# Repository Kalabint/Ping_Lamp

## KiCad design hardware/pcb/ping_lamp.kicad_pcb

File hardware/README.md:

# Ping Lamp hardware: driver board and base for a Harmony XVU tower

Round driver PCB (54 mm) and a 3D-printed base ring (60 mm) that sit between a base plate and a
Schneider Electric Harmony XVU signal tower with 24 V AC/DC red, orange and green units.
One USB cable supplies the lamp and is also the programming port.

## Status

| Item | State |
|---|---|
| Netlist | Checked by script: schematic = PCB = `pcb/design.py` (131 pins) |
| Routing | Complete, 0 unconnected, 68 ground stitching vias |
| DRC (KiCad 7.0.11) | No clearance, short or edge errors. A few silkscreen notes. The 47 `lib_footprint_issues` entries in `pcb/fab/ping_lamp_drc.txt` only say that the build machine had no footprint library table. |
| Independent review | One review by a second reviewer without access to the design history; its findings are fixed or listed under "Open points" |
| Prototype | **None built.** Nothing here has been tested on hardware. |

Read "Open points" before ordering.

## Files

| Path | Content |
|---|---|
| [`docs/datasheet.md`](docs/datasheet.md) | Datasheet: ratings, electrical design values, connectors, mechanical data |
| [`docs/manual.md`](docs/manual.md) | Assembly and operating manual |
| `pcb/design.py` | Parts, netlist, placement, pre-laid tracks. Edit this, not the KiCad files. |
| `pcb/generate.py` | Builds schematic, routed PCB and `pcb/fab/` from `design.py` |
| `pcb/ping_lamp.kicad_*` | KiCad 7 project (generated) |
| `pcb/fab/ping_lamp_gerber.zip` | Gerber and drill files |
| `pcb/fab/ping_lamp_bom.csv`, `ping_lamp_cpl.csv` | Parts list and placement file in JLCPCB column layout |
| `pcb/fab/*.pdf` | Schematic and both copper sides |
| `enclosure/ping_lamp_base.scad` | Parametric base ring (OpenSCAD) |
| `enclosure/*.stl` | Tray and lid, exported with the default parameters |

## Circuit

| Block | Parts | Notes |
|---|---|---|
| Input | USB-C (J1), 5.1 k on CC1/CC2, PTC fuse 1.1 A (F1), USBLC6-2SC6 (U4) | Optional solder pads J4 "5V IN" in parallel to USB VBUS |
| 3.3 V | AP2112K-3.3 (U2) | Supplies the ESP32 module |
| 24 V | MT3608 boost (U3), 22 uH (L1), SS34 (D1), 390 k / 10 k divider | Vout = 0.6 V x (1 + 390/10) = 24.0 V. Enable is pulled down: the rail is **off until the firmware drives GPIO10 high** |
| Controller | ESP32-C3-WROOM-02-N4 (U1) | Native USB serial/JTAG on GPIO18/19, no USB-UART bridge |
| Outputs | 4 x AO3422 low-side (Q1..Q4), 100 R gate, 10 k pull-down | Tower common is +24 V, each tier returns through one MOSFET |

With the boost disabled the "+24V" terminal still carries about 4.5 V (USB voltage through L1
and D1). That is how a boost converter behaves; it is not a fault.

### GPIO map

| GPIO | Function |
|---|---|
| 4 | Green tier (Q1) |
| 5 | Orange tier (Q2) |
| 6 | Red tier (Q3) |
| 7 | AUX output (Q4), e.g. buzzer unit |
| 10 | Boost enable, high = 24 V on |
| 8 | Status LED, active low (strapping pin, pulled up) |
| 9 | BOOT button (SW1) |
| 0, 1 | Expansion header J3 (IO0, IO1, 3V3, GND), not populated |
| 2 | Pulled up (strapping pin) |

Firmware: in `ESP32/main.py` set `PIN_NUM_GREEN = 4`, `PIN_NUM_ORANGE = 5`, `PIN_NUM_RED = 6`,
`PIN_NUM_BOOST_EN = 10` and flash the MicroPython build for ESP32-C3. The defaults in that
file are for the breadboard version; on this board they would drive the USB pins.

### Terminal J2 (wire entry faces the board centre)

Seen from the component side with the terminal at the bottom, left to right:

| 24V | AUX | R | O | G |
|---|---|---|---|---|
| tower common | spare | red return | orange return | green return |

The labels are printed on both sides of the board.

### Power budget

| Case | 24 V load | USB current at 5 V (estimate) |
|---|---|---|
| One tier on (normal fade: duties add up to one tier) | 40 to 50 mA | 0.35 to 0.45 A |
| All three tiers on | about 140 mA | about 1.0 A |

- The whole 24 V rail, tiers and AUX together, is good for about 150 mA. Inductor (1.0 A rated)
  and fuse (1.1 A hold) set that limit.
- "All tiers on" is a test case, not a continuous mode: the fuse hold current drops in a warm,
  closed housing.
- AUX is meant for one more XVU unit (buzzer or fourth light, about 50 mA). An inductive load
  needs an external flyback diode.
- Tier currents are from Schneider datasheet extracts (XVUC23 max. 50 mA, XVUC24 max. 40 mA);
  the orange unit is assumed to be similar. Converter efficiency is assumed at 85 %.
- Use a charger rated for at least 1 A.

## Ordering the board

Placing the order is manual; nothing in this repository orders anything.

1. Upload `pcb/fab/ping_lamp_gerber.zip`. 2 layers, 1.6 mm, any colour.
2. Select SMT assembly, top side. Upload `ping_lamp_bom.csv` and `ping_lamp_cpl.csv`.
3. In the parts matching step, check every line against the "LCSC number check" column
   ("search snippet" = seen in a search result, not on the live page; "unchecked" = from memory).
   **Do not confirm the order with R8 (390 k) unmatched or substituted by another value.** R8
   sets the output voltage; without it the converter has no feedback and destroys itself.
4. Check the rotation of every polarised part in the placement preview. KiCad and JLCPCB use
   different zero-rotation conventions for some packages, and the placement file carries the
   KiCad values. U3 and U4 (SOT-23-6) are the critical ones: they also fit their pads when
   turned by 180 degrees, which reverses their supply pins. Pin 1 is marked on the silkscreen.
5. Solder by hand after delivery: J2 (5-position screw terminal, 3.5 mm pitch).
   J3 and J4 stay empty unless needed.

### Parts that are not on the board

| Qty | Part |
|---|---|
| 1 | Screw terminal block, 5 positions, 3.5 mm pitch, through-hole (Phoenix PT 1,5/5-3.5-H or equivalent; compare the footprint drawing) |
| 4 | Countersunk screw M3 x 25. Nylon at the two holes beside the antenna (H1, H2) reduces detuning |
| 2 | Countersunk wood screw 3.5 to 4 mm for the tray |
| n | Screws for the tower base according to the XVU base (default model: 3 x M4, at most 8 mm of thread below the tower base). Optional: M4 heat-set inserts |
| 1 | USB-C cable, right-angle plug recommended, and a USB charger of at least 1 A |
| - | 4 wires, 0.25 to 0.5 mm2, from J2 to the terminals in the tower base |

## Base ring

Stack from the base plate upwards: tray floor 3 mm, 4 mm clearance, PCB 1.6 mm, 11.5 mm
component space, lid 5.5 mm. Total 25.6 mm, diameter 60 mm.

- **Tray:** screwed to the base plate from the inside, USB opening 13 x 7.5 mm in the wall, with
  a recess above it so the PCB drops straight in.
- **Lid:** four spacer tubes press the PCB onto the tray bosses. The wall ends 0.2 mm below the
  lid so that the tubes, not the wall, take the screw force. The screw heads end up under the
  tower base.
- **Tower fixing:** the tower screws cut their own thread in the lid (`tower_fix = "thread"`),
  or go into heat-set inserts (`"insert"`). There are no loose nuts above the PCB.
- **Print:** tray as modelled, lid upside down (STL is already turned). No supports.
  0.2 mm layers, 3 or more perimeters, PETG or PLA.
- **Cable from below instead of a plug:** set `floor_cable_hole_d` and solder the cable to J4.

Assembly order: tray onto the base plate, PCB with the four tower wires already in J2 into the
tray, wires through the lid's centre hole, lid on with the four M3 screws, tower base onto the
lid, wires into the tower terminals.

BOOT and RESET sit under the centre hole. They are reachable with a thin rod while the tower
base is off. Keep the wire slack away from them: a wire resting on RESET holds the board in
reset.

**The tower interface values in the SCAD file are placeholders.** No dimension drawing of the
XVU base could be retrieved. Measure on the real base and set `tower_d`, `tower_cable_hole_d`,
`tower_bolt_count`, `tower_bolt_circle` and `tower_bolt_angle`, then export both parts again.
OpenSCAD stops with an error if a tower screw would hit a spacer tube. Keep tower screws out
of the +y direction as well; that is where the antenna is.

## Bring-up

1. Plug in USB without the tower connected. Measure 3.3 V at J3 (pin 3 to pin 4).
2. Hold BOOT, press RESET, release BOOT. Flash MicroPython for ESP32-C3.
3. In the REPL switch the rail on and measure 23 to 25 V between J2 "24V" and GND:
   `from machine import Pin; Pin(10, Pin.OUT, value=1)`
4. Copy the firmware with the four pin constants set as above.
5. Connect one tier only, tower common to "24V". If it stays dark with the output switched
   on, the unit is polarity sensitive in the other direction; see open points.
6. Test the fade. If the tier flickers or does not dim, lower `PWM_FREQUENCY` (100 to 200 Hz)
   or switch the firmware to stepped on/off states.

## Open points

| Topic | Risk |
|---|---|
| PWM dimming of XVU LED units | Schneider documents are silent. The units contain their own AC/DC input stage; a smooth green-orange-red fade is not guaranteed. **Test one unit with a MOSFET and a 24 V supply before ordering the board.** |
| Polarity | The board switches the negative side; common must accept +24 V. Unconfirmed for the XVU base in use. A base that needs common on 0 V cannot be driven by this board without changes. |
| No over-voltage clamp on the 24 V rail | If R8 is missing or open the boost converter runs away. Covered only by the BOM check above. |
| Placement rotations | Not corrected for JLCPCB conventions, because those could not be verified from here. Manual check in the preview is required. |
| Footprints of substitute parts | USB-C, tactile switch, inductor and module footprints are the KiCad library ones for the named parts; the LCSC parts were not checked against their drawings. |
| Datasheets | Manufacturer sites were not reachable. Not confirmed against a datasheet: AO3422 pin drawing (standard SOT-23 order assumed; order the genuine AOS part), MT3608 absolute maximum ratings and soft start. |
| Inrush at plug-in | About 50 uF sits behind the fuse. A weak USB port may briefly dip. The boost itself starts only when the firmware enables it. |
| Boost layout | Autorouted, not hand-optimised for switching-node area. EMC was not assessed. |
| Bottom ground plane | Cut by one 2.5 mm wide bundle of five signal tracks under the module and by the 5 V feed. Stitching vias sit on both sides. |
| Antenna | Ground pour starts 14 mm either side of the antenna, steel screws at H1/H2 are 13 mm away. A metal base plate would detune it further. |
| Thermal vias of the module pad | The 0.2 mm vias of the library footprint are removed; four 0.3 mm stitching vias sit around the pad instead. |

## Regenerating

Needs KiCad 7 with its Python module, Java, and a Freerouting jar (1.9.0 was used).

```bash
/usr/bin/python3 hardware/pcb/generate.py --freerouting /path/to/freerouting.jar
```

- The build happens in a scratch directory. The files in the repository are replaced only if
  the netlist check passes, nothing is unrouted and DRC shows no entry other than silkscreen
  notes. A rejected build prints `BUILD REJECTED` and leaves the repository untouched.
- The autorouter does not give the same result every run and can fail to complete a net.
  The 5 V feed, the reset line and the four gate lines are pre-laid in `design.py` for that
  reason. If a build is rejected, run it again or pre-lay the failing net.
- `--reuse-session` reuses the stored routing only if placement and netlist are unchanged.
- KiCad 7 has no command-line ERC; open the schematic in KiCad to run it.

```bash
openscad -D 'part="tray"' -o hardware/enclosure/ping_lamp_base_tray.stl hardware/enclosure/ping_lamp_base.scad
```

```bash
openscad -D 'part="lid"' -o hardware/enclosure/ping_lamp_base_lid.stl hardware/enclosure/ping_lamp_base.scad
```

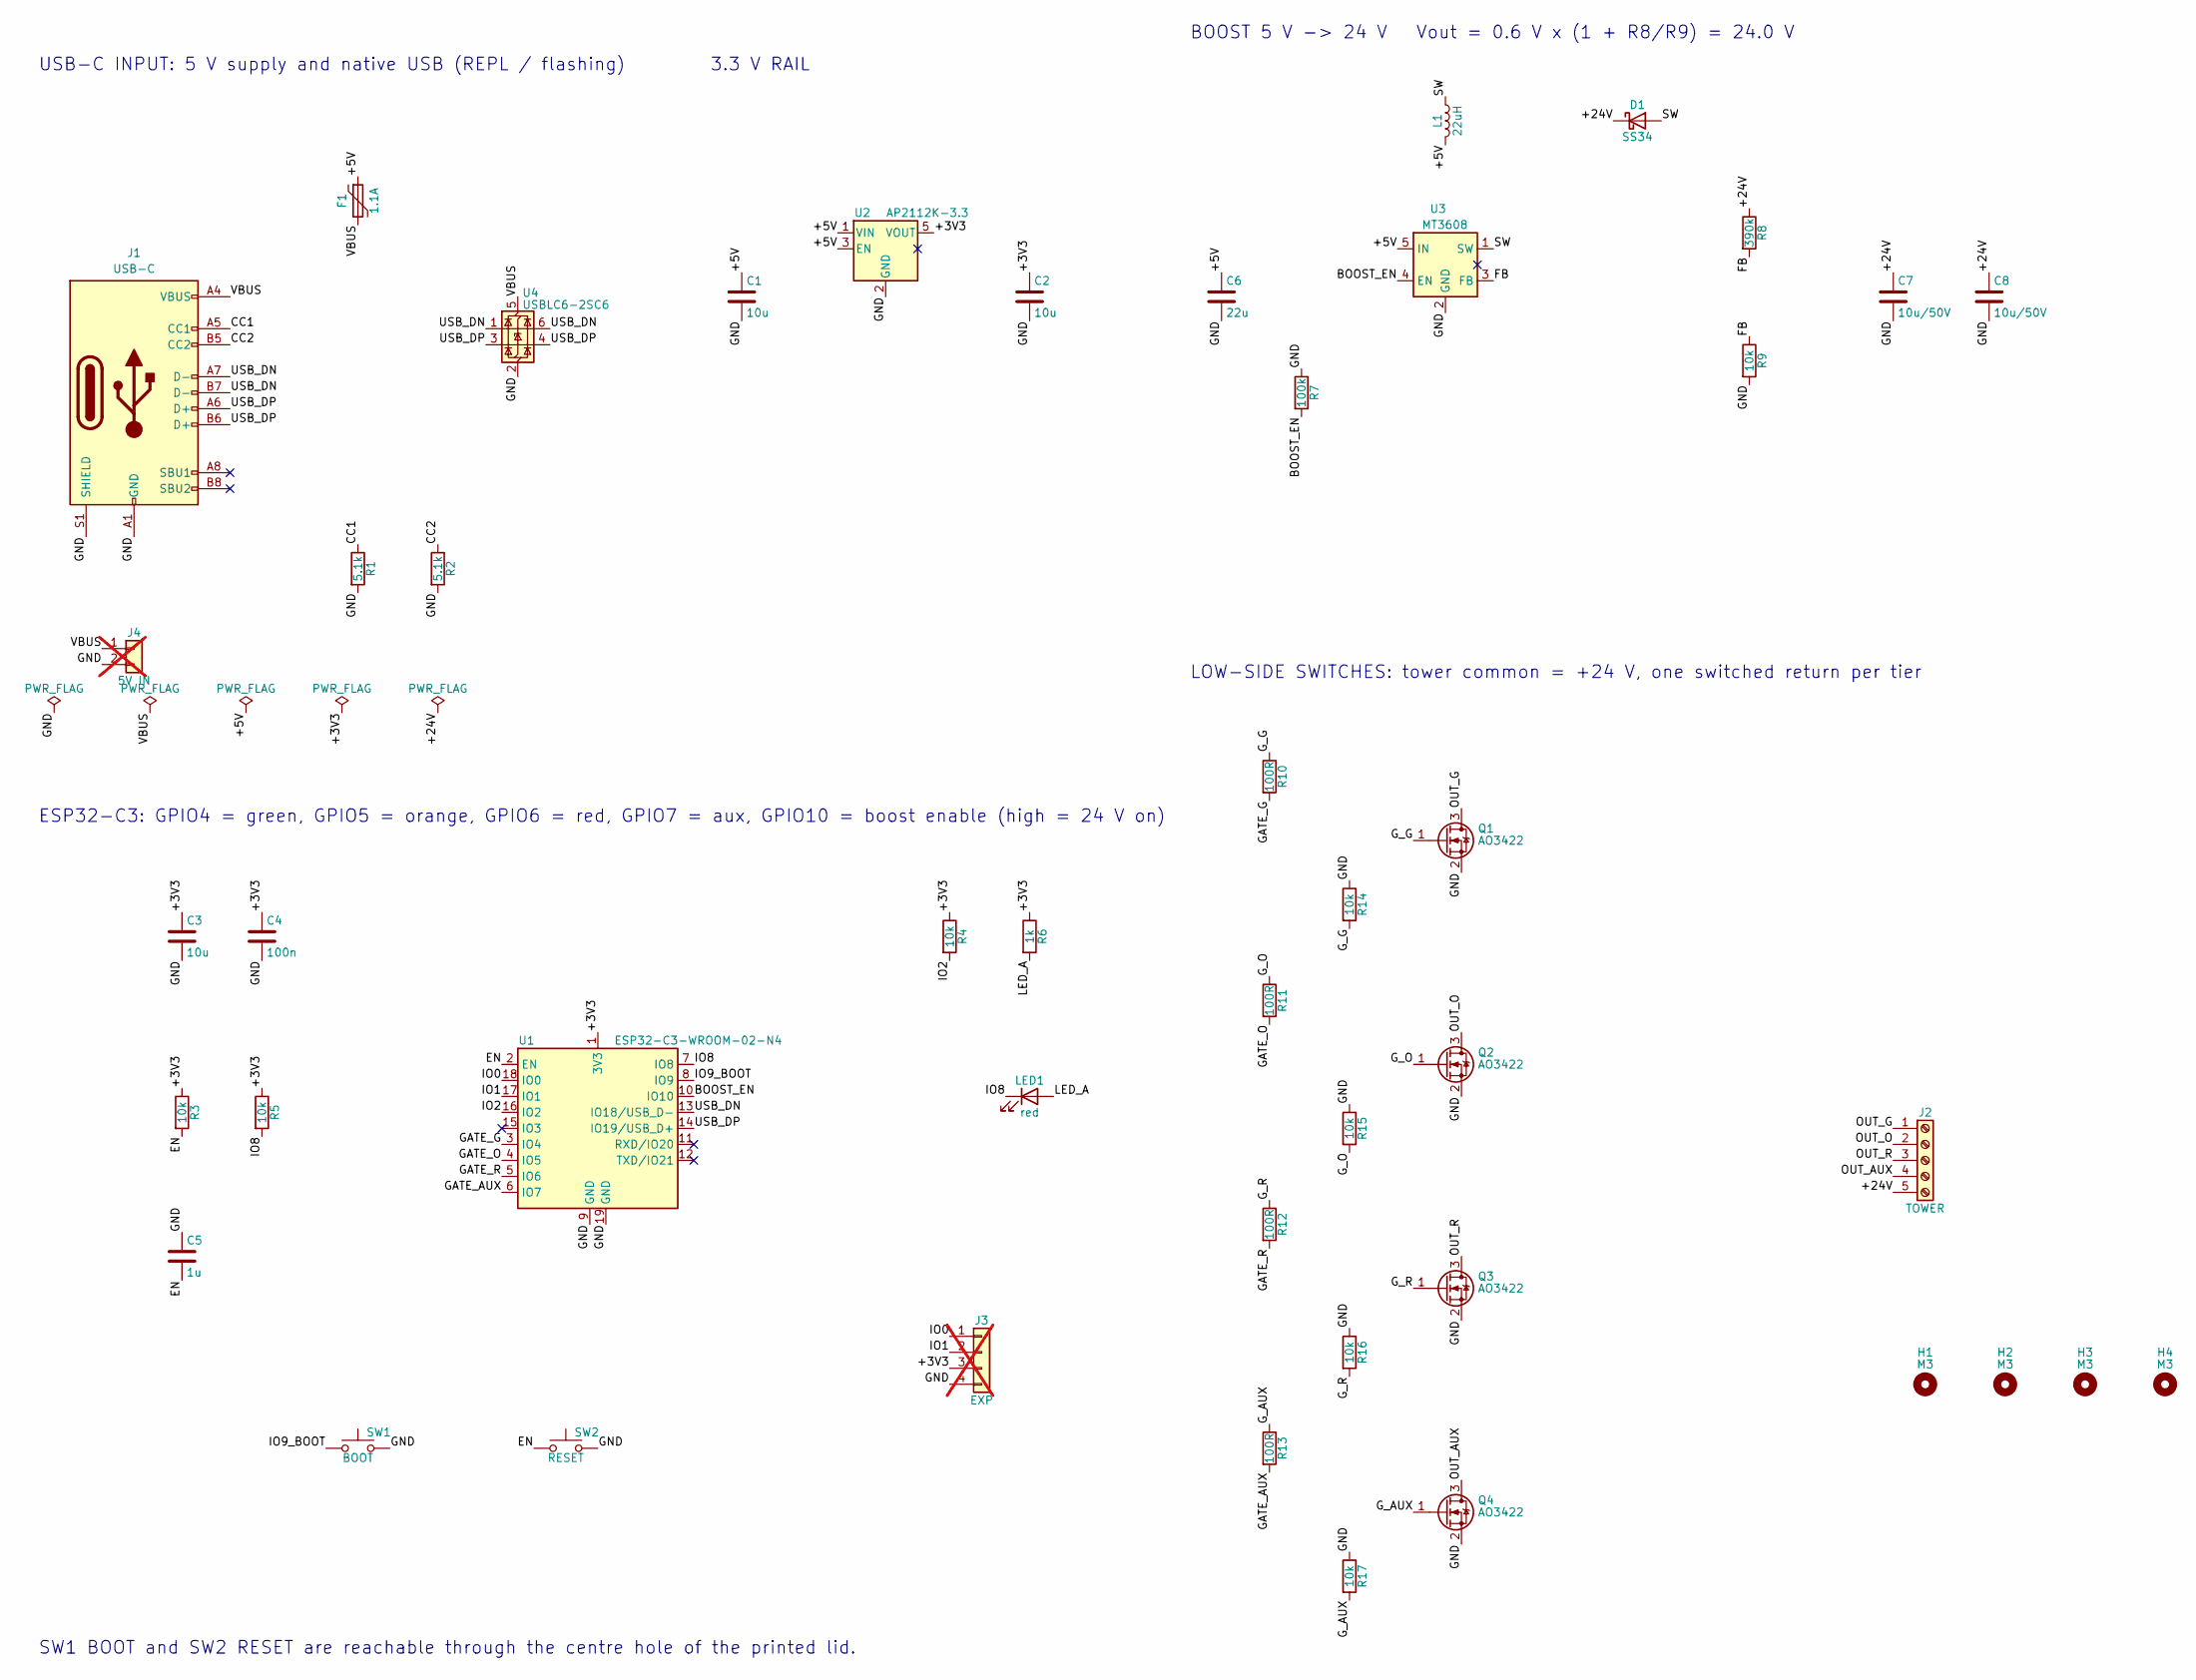
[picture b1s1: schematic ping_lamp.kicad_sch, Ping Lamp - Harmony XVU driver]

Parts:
C1, C2, C3: 10u; C_0805_2012Metric; MPN CL21A106KAYNNNE; LCSC C15850
C4: 100n; C_0603_1608Metric; MPN CC0603KRX7R9BB104; LCSC C14663
C5: 1u; C_0603_1608Metric; MPN CL10A105KB8NNNC; LCSC C15849
C6: 22u; C_0805_2012Metric; MPN CL21A226MAQNNNE; LCSC C45783
C7, C8: 10u/50V; C_1206_3216Metric; MPN CL31A106KBHNNNE; LCSC C13585
D1: SS34; D_SMA; MPN SS34; LCSC C8678
F1: 1.1A; Fuse_1812_4532Metric; MPN BSMD1812-110-33V; LCSC C883150
H1, H2, H3, H4: M3; MountingHole_3.2mm_M3
J1: USB-C; USB_C_Receptacle_HRO_TYPE-C-31-M-12; MPN TYPE-C-31-M-12; LCSC C165948
J2: TOWER; TerminalBlock_Phoenix_PT-1,5-5-3.5-H_1x05_P3.50mm_Horizontal; MPN 5-pos screw terminal 3.5 mm pitch (Phoe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
J3: EXP; PinHeader_1x04_P2.54mm_Vertical; MPN 1x4 pin header 2.54 mm; not fitted
J4: 5V IN; PinHeader_1x02_P2.54mm_Vertical; MPN 2 solder pads 2.54 mm; not fitted
L1: 22uH; L_Sunlord_SWPA4030S; MPN SWPA4030S220MT; LCSC C83472
LED1: red; LED_0603_1608Metric; MPN KT-0603R; LCSC C2286
Q1, Q2, Q3, Q4: AO3422; SOT-23; MPN AO3422; LCSC C37130
R1, R2: 5.1k; R_0603_1608Metric; MPN 0603WAF5101T5E; LCSC C23186
R3, R4, R5, R9, R14, R15, R16, R17: 10k; R_0603_1608Metric; MPN 0603WAF1002T5E; LCSC C25804
R6: 1k; R_0603_1608Metric; MPN 0603WAF1001T5E; LCSC C21190
R7: 100k; R_0603_1608Metric; MPN 0603WAF1003T5E; LCSC C25803
R8: 390k; R_0603_1608Metric; MPN 0603WAF3903T5E; LCSC C23150
R10, R11, R12, R13: 100R; R_0603_1608Metric; MPN 0603WAF1000T5E; LCSC C22775
SW1: BOOT; SW_Push_1P1T_XKB_TS-1187A; MPN TS-1187A-B-A-B; LCSC C318884
SW2: RESET; SW_Push_1P1T_XKB_TS-1187A; MPN TS-1187A-B-A-B; LCSC C318884
U1: ESP32-C3-WROOM-02-N4; ESP32-C3-WROOM-02; MPN ESP32-C3-WROOM-02-N4; LCSC C2934560
U2: AP2112K-3.3; SOT-23-5; MPN AP2112K-3.3TRG1; LCSC C51118
U3: MT3608; SOT-23-6; MPN MT3608; LCSC C84817
U4: USBLC6-2SC6; SOT-23-6; MPN USBLC6-2SC6; LCSC C7519

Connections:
+3V3: C2.1, C3.1, C4.1, J3.3, R3.1, R4.1, R5.1, R6.1, U1.1 (3V3), U2.5 (VOUT)
+5V: C1.1, C6.1, F1.1, L1.2, U2.1 (VIN), U2.3 (EN), U3.5 (IN)
+24V: C7.1, C8.1, D1.1 (K), J2.5, R8.1
BOOST_EN: R7.2, U1.10 (IO10), U3.4 (EN)
CC1: J1.A5 (CC1), R1.1
CC2: J1.B5 (CC2), R2.1
EN: C5.2, R3.2, SW2.1, U1.2 (EN)
FB: R8.2, R9.1, U3.3 (FB)
GATE_AUX: R13.2, U1.6 (IO7)
GATE_G: R10.2, U1.3 (IO4)
GATE_O: R11.2, U1.4 (IO5)
GATE_R: R12.2, U1.5 (IO6)
GND: C1.2, C2.2, C3.2, C4.2, C5.1, C6.2, C7.2, C8.2, J1.A1 (GND), J1.A12 (GND), J1.B1 (GND), J1.B12 (GND), J1.S1 (SHIELD), J3.4, J4.2, Q1.2 (S), Q2.2 (S), Q3.2 (S), Q4.2 (S), R1.2, R2.2, R7.1, R9.2, R14.1, R15.1, R16.1, R17.1, SW1.2, SW2.2, U1.9 (GND), U1.19 (GND), U2.2 (GND), U3.2 (GND), U4.2 (GND)
G_AUX: Q4.1 (G), R13.1, R17.2
G_G: Q1.1 (G), R10.1, R14.2
G_O: Q2.1 (G), R11.1, R15.2
G_R: Q3.1 (G), R12.1, R16.2
IO0: J3.1, U1.18 (IO0)
IO1: J3.2, U1.17 (IO1)
IO2: R4.2, U1.16 (IO2)
IO8: LED1.1 (K), R5.2, U1.7 (IO8)
IO9_BOOT: SW1.1, U1.8 (IO9)
LED_A: LED1.2 (A), R6.2
OUT_AUX: J2.4, Q4.3 (D)
OUT_G: J2.1, Q1.3 (D)
OUT_O: J2.2, Q2.3 (D)
OUT_R: J2.3, Q3.3 (D)
SW: D1.2 (A), L1.1, U3.1 (SW)
USB_DN: J1.A7 (D-), J1.B7 (D-), U1.13 (IO18/USB_D-), U4.1 (I/O1), U4.6 (I/O1)
USB_DP: J1.A6 (D+), J1.B6 (D+), U1.14 (IO19/USB_D+), U4.3 (I/O2), U4.4 (I/O2)
VBUS: F1.2, J1.A4 (VBUS), J1.A9 (VBUS), J1.B4 (VBUS), J1.B9 (VBUS), J4.1, U4.5 (VBUS)

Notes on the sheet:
USB-C INPUT: 5 V supply and native USB (REPL / flashing)
3.3 V RAIL
BOOST 5 V -> 24 V Vout = 0.6 V x (1 + R8/R9) = 24.0 V
ESP32-C3: GPIO4 = green, GPIO5 = orange, GPIO6 = red, GPIO7 = aux, GPIO10 = boost enable (high = 24 V on)
LOW-SIDE SWITCHES: tower common = +24 V, one switched return per tier
SW1 BOOT and SW2 RESET are reachable through the centre hole of the printed lid.

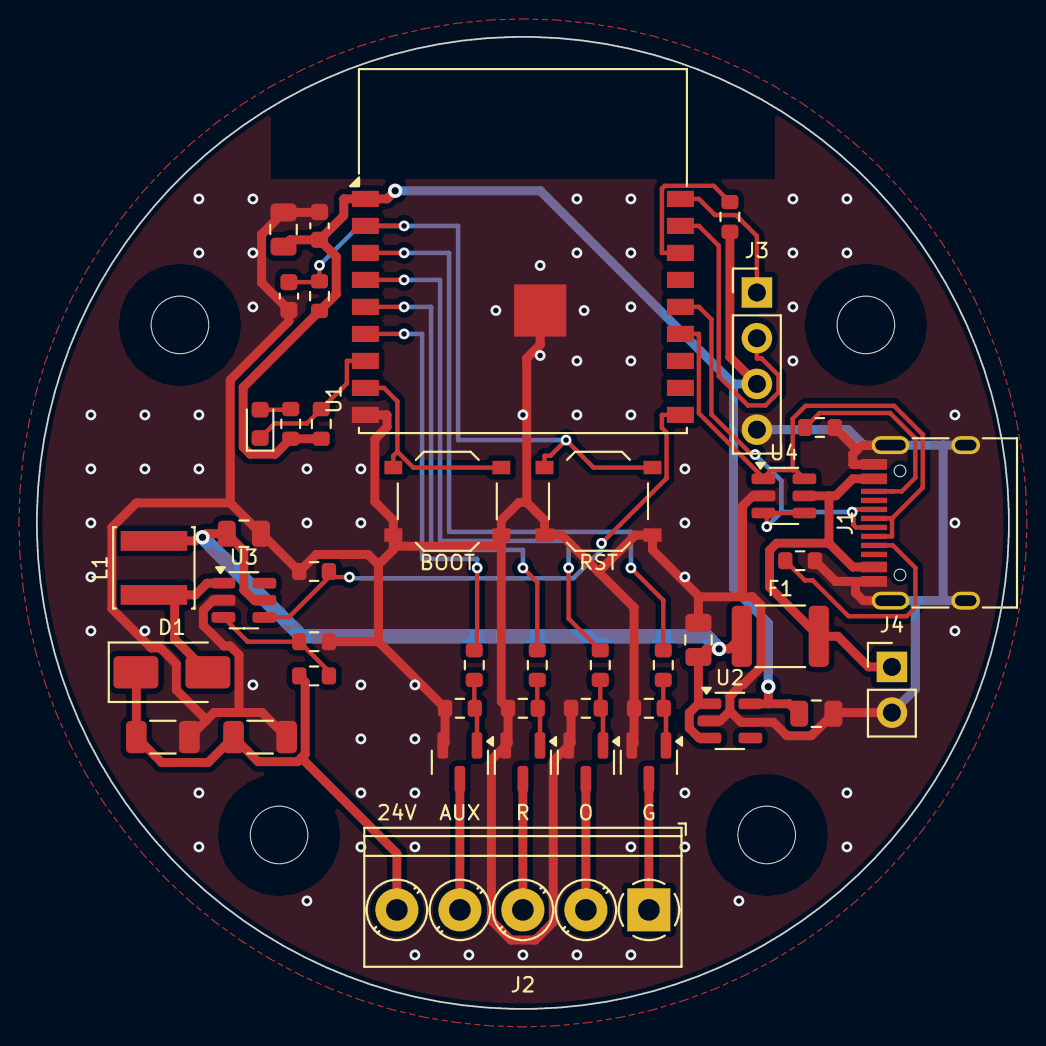
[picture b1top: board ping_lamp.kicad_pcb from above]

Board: 2 copper layers, 54.0 x 54.0 mm, 47 parts (0 on the bottom side), 31 nets.

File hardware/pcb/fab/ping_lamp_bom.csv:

Comment,Designator,Footprint,LCSC Part #,MPN,Description,Qty,Assembly,LCSC number check
USB-C,J1,USB_C_Receptacle_HRO_TYPE-C-31-M-12,C165948,TYPE-C-31-M-12,USB-C receptacle 16P USB 2.0,1,SMT (fab),search snippet
5.1k,"R1,R2",R_0603_1608Metric,C23186,0603WAF5101T5E,Resistor 5.1 k 1 % 0603,2,SMT (fab),search snippet
1.1A,F1,Fuse_1812_4532Metric,C883150,BSMD1812-110-33V,PTC fuse 1.1 A hold 33 V 1812,1,SMT (fab),search snippet
USBLC6-2SC6,U4,SOT-23-6,C7519,USBLC6-2SC6,USB ESD protection SOT-23-6,1,SMT (fab),search snippet
5V IN,J4,PinHeader_1x02_P2.54mm_Vertical,,2 solder pads 2.54 mm,"Alternative 5 V wire entry, not populated",1,not populated,select manually
AP2112K-3.3,U2,SOT-23-5,C51118,AP2112K-3.3TRG1,LDO 3.3 V 600 mA SOT-23-5,1,SMT (fab),search snippet
10u,"C1,C2,C3",C_0805_2012Metric,C15850,CL21A106KAYNNNE,Capacitor 10 uF 25 V X5R 0805,3,SMT (fab),search snippet
MT3608,U3,SOT-23-6,C84817,MT3608,Boost converter 1.2 MHz SOT-23-6,1,SMT (fab),unchecked
22uH,L1,L_Sunlord_SWPA4030S,C83472,SWPA4030S220MT,Inductor 22 uH 1.3 A sat. 4x4x3 mm,1,SMT (fab),search snippet
SS34,D1,D_SMA,C8678,SS34,Schottky 40 V 3 A SMA,1,SMT (fab),search snippet
22u,C6,C_0805_2012Metric,C45783,CL21A226MAQNNNE,Capacitor 22 uF 25 V X5R 0805,1,SMT (fab),search snippet
10u/50V,"C7,C8",C_1206_3216Metric,C13585,CL31A106KBHNNNE,Capacitor 10 uF 50 V X5R 1206,2,SMT (fab),search snippet
100k,R7,R_0603_1608Metric,C25803,0603WAF1003T5E,Resistor 100 k 1 % 0603,1,SMT (fab),search snippet
390k,R8,R_0603_1608Metric,C23150,0603WAF3903T5E,Resistor 390 k 1 % 0603,1,SMT (fab),search snippet
10k,"R9,R3,R4,R5,R14,R15,R16,R17",R_0603_1608Metric,C25804,0603WAF1002T5E,Resistor 10 k 1 % 0603,8,SMT (fab),search snippet
ESP32-C3-WROOM-02-N4,U1,ESP32-C3-WROOM-02,C2934560,ESP32-C3-WROOM-02-N4,ESP32-C3 module 4 MB flash,1,SMT (fab),search snippet
100n,C4,C_0603_1608Metric,C14663,CC0603KRX7R9BB104,Capacitor 100 nF 50 V X7R 0603,1,SMT (fab),search snippet
1u,C5,C_0603_1608Metric,C15849,CL10A105KB8NNNC,Capacitor 1 uF 50 V X5R 0603,1,SMT (fab),search snippet
1k,R6,R_0603_1608Metric,C21190,0603WAF1001T5E,Resistor 1 k 1 % 0603,1,SMT (fab),search snippet
red,LED1,LED_0603_1608Metric,C2286,KT-0603R,LED red 0603,1,SMT (fab),search snippet
BOOT,SW1,SW_Push_1P1T_XKB_TS-1187A,C318884,TS-1187A-B-A-B,Tactile switch 5.1x5.1 mm SMD,1,SMT (fab),search snippet
RESET,SW2,SW_Push_1P1T_XKB_TS-1187A,C318884,TS-1187A-B-A-B,Tactile switch 5.1x5.1 mm SMD,1,SMT (fab),search snippet
EXP,J3,PinHeader_1x04_P2.54mm_Vertical,,1x4 pin header 2.54 mm,"Expansion header, not populated",1,not populated,select manually
AO3422,"Q1,Q2,Q3,Q4",SOT-23,C37130,AO3422,N-MOSFET 55 V 2.1 A SOT-23 (genuine AOS),4,SMT (fab),search snippet
100R,"R10,R11,R12,R13",R_0603_1608Metric,C22775,0603WAF1000T5E,Resistor 100 R 1 % 0603,4,SMT (fab),search snippet
TOWER,J2,"TerminalBlock_Phoenix_PT-1,5-5-3.5-H_1x05_P3.50mm_Horizontal",,"5-pos screw terminal 3.5 mm pitch (Phoenix PT 1,5/5-3.5-H or equiv.)","Terminal block 5 x 3.5 mm, THT, hand soldered",1,THT (by hand),select manually
